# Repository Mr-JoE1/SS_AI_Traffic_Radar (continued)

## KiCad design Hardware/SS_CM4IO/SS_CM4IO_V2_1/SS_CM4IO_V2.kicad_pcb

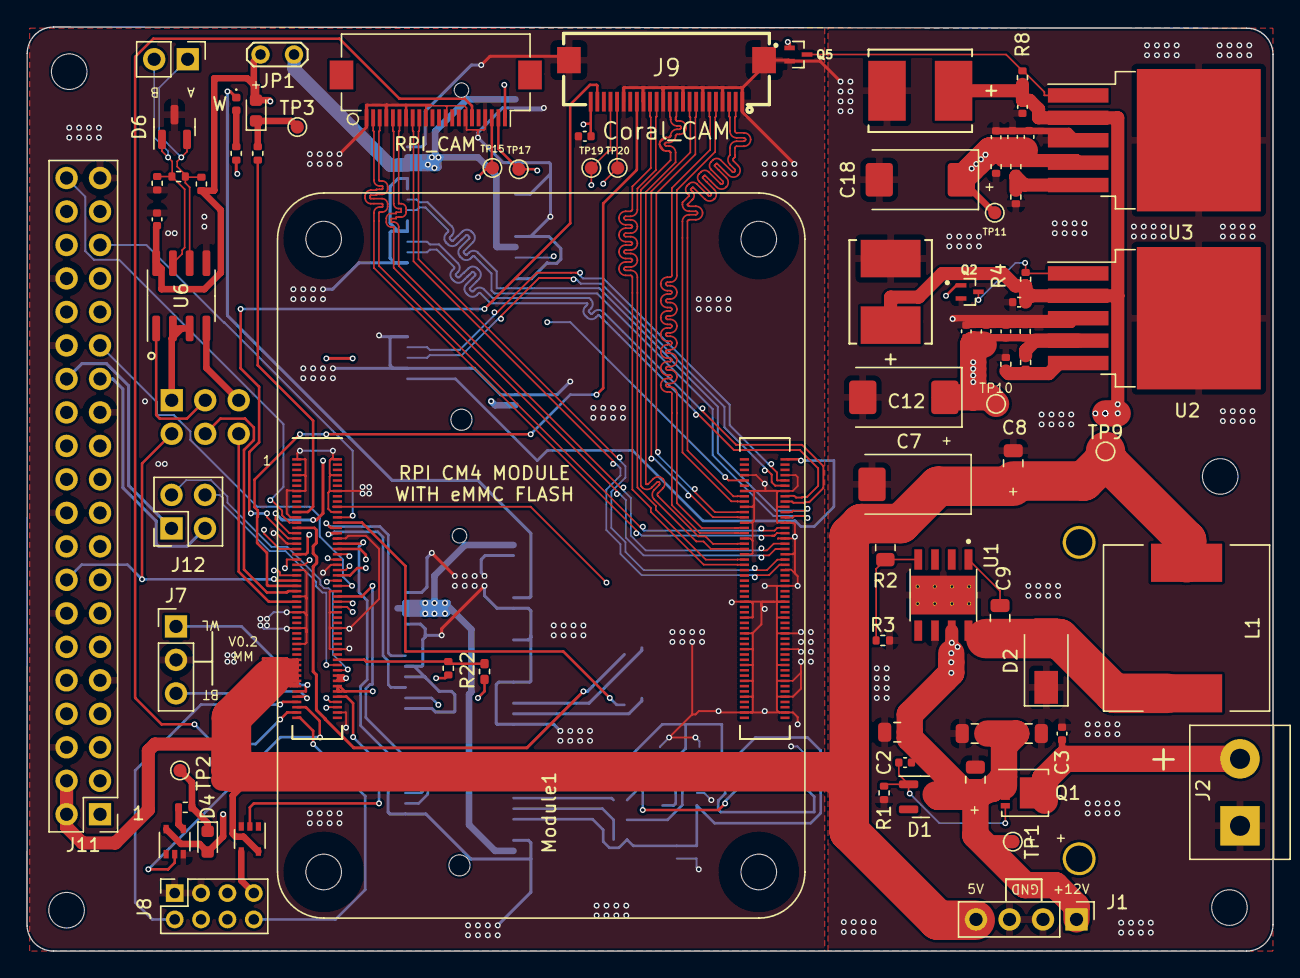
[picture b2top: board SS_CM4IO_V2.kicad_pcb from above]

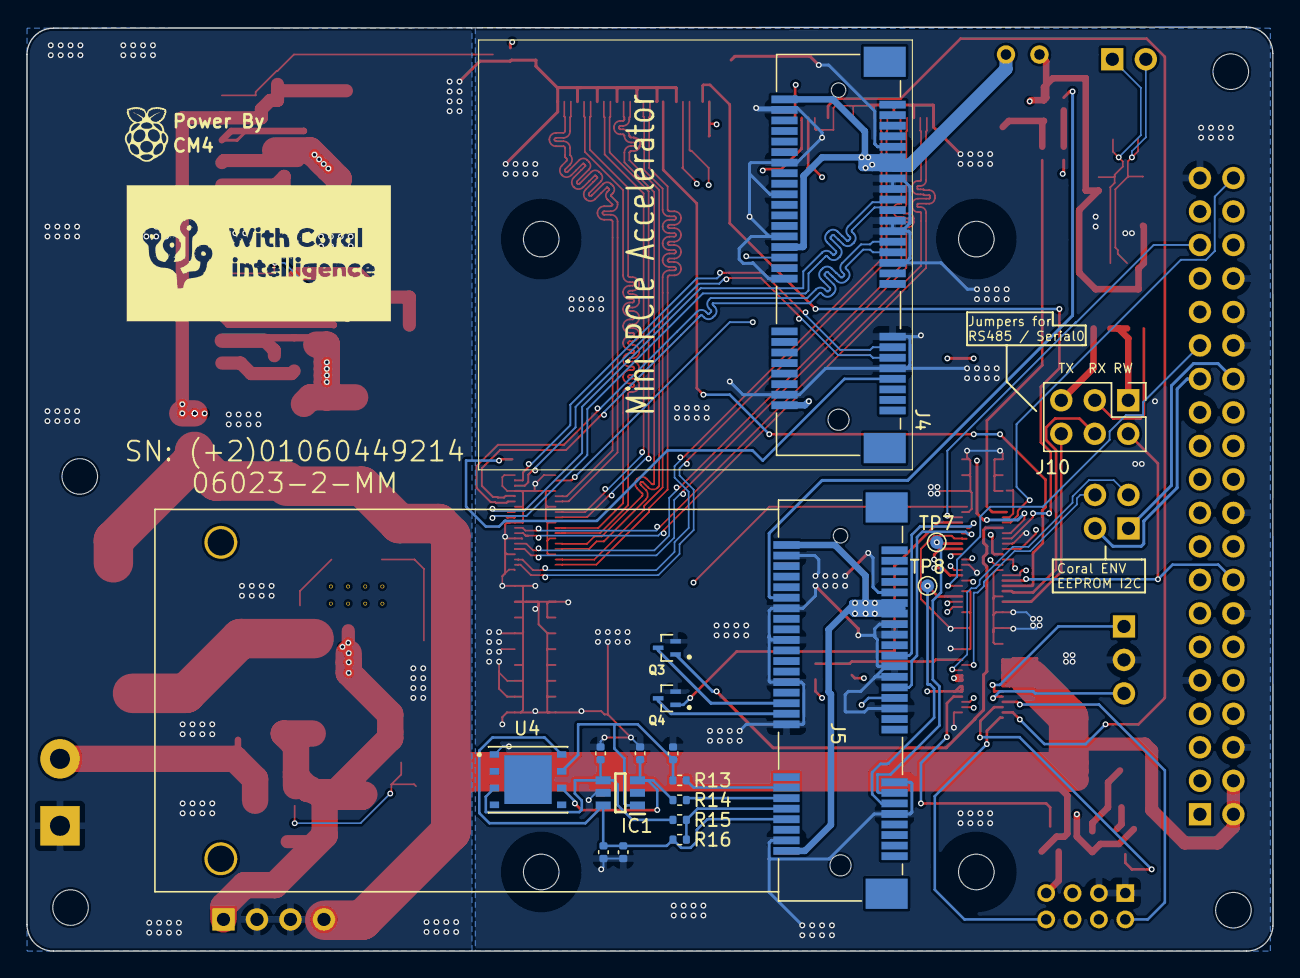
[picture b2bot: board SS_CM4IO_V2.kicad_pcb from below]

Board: 4 copper layers, 94.5 x 70.1 mm, 103 parts (18 on the bottom side), 47 nets.

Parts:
C1: 10u 35v; C_0805_2012Metric
C2, C3: 100n 100v; C_0402_1005Metric
C4, C5: 4.7uF; C_0805_2012Metric
C6, C8, C9: 0.01uF; C_0805_2012Metric
C7: 330uF; CP_EIA-7343-31_Kemet-D
C10, C16: 470uF; Kemet _3760_H
C11, C13, C17, C19, C26: 100n; C_0402_1005Metric
C12, C18: 470uF; CP_EIA-7343-31_Kemet-D
C14, C20, C22, C23, C24, C25: 33p; C_0402_1005Metric
C15, C21: 10p; C_0402_1005Metric
C27: 104; C_0402_1005Metric
C28: 1u; C_0402_1005Metric
CM4_A, CM4_B: DF40C-100DS; DF40C-100DS_CM4
D1: MMBZ5242BLT1G; SOT-23
D2: SS54; D_SMA
D3: W; LED_0402_1005Metric
D4: LED Red; LED_0603_1608Metric
D5: LED Green; LED_0603_1608Metric
D6: PSM712-LF-T7; SOT-23
H1, H2, H3, H4: MountingHole; MountingHole_2.7mm_M2.5
IC1: DALC208SC6; SOT95P280X145-6N
J1: AMP171826-4; PinHeader_1x04_P2.54mm_Vertical
J2: pwr; TerminalBlock_bornier-2_P5.08mm
J3: RPI_CAM; Hirose_FH12-22S-0.5SH_1x22-1MP_P0.50mm_Horizontal
J4, J5: Bus_PCI_Express_Mini; BUS_PCI_Express_Mini_Half
J6: Conn_01x02_Male; PinHeader_1x02_P2.54mm_Vertical
J7: W.BT; PinHeader_1x03_P2.54mm_Vertical
J8: Conn_02x04_Odd_Even; PinSocket_2x04_P2.00mm_Vertical
J9: Coral_CAM; FPC-SMD_P0.50-24P_QCHF-SM-H2.0
J10: RADAR_EN; PinHeader_2x03_P2.54mm_Vertical
J11: ENV_SEN; PinHeader_2x20_P2.54mm_Vertical
J12: EPP_RW; PinSocket_2x02_P2.54mm_Vertical
JP1: Jumper_2_Open; TestPoint_2Pads_Pitch2.54mm_Drill0.8mm
L1: CDRH127/LDNP-150MC; L_12x12mm_H8mm
Module1: ComputeModule4; Raspberry-Pi-4-Compute-Module
Q1: DMP3013SFV-7; Diodes_PowerDI3333-8
Q2, Q3, Q4, Q5: DTC143ZEBTL; SOTFL50P160X85-3N
R1: 12K 1%; R_0402_1005Metric
R2: 10K; R_0805_2012Metric
R3: 3.16K; R_0402_1005Metric
R4, R8: 51K; R_0402_1005Metric
R5, R9: 82K 1%; R_0402_1005Metric
R6, R10: 470R; R_0402_1005Metric
R7, R11: 47K 1%; R_0402_1005Metric
R12: 1K; R_0402_1005Metric
R13, R14, R15: 22R; R_0402_1005Metric
R16: 15R; R_0402_1005Metric
R17, R18: 1k; R_0402_1005Metric
R19, R20: 360R; R_0402_1005Metric
R21: 0R; R_0402_1005Metric
R22: nf; R_0402_1005Metric_Pad0.72x0.64mm_HandSolder
R23: 120R; R_0402_1005Metric
TP1: 12V; TestPoint_Pad_D1.0mm
TP2, TP3, TP7, TP8, TP9, TP10, TP11, TP15, TP17, TP19, TP20: TestPoint; TestPoint_Pad_D1.0mm
U1: TPS5450DDAR; CONV_TPS5450DDAR
U2, U3: MIC29302WU; TO-263-5_TabPin3
U4: SIM-E-MFF2-GL-250; PSON127P500X600X82-9N
U5, U7: 74LVC1G07SE-7; SOT-353_SC-70-5
U6: MAX3485; SOIC-8_3.9x4.9mm_P1.27mm

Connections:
/4G_GSM/+3v3_GSM: C18.1, C19.1, C20.1, C21.1, J5.2 (+3V3AUX), J5.39 (+3V3AUX), J5.41 (+3V3AUX), J5.52 (+3V3AUX), R9.1, R10.1, R12.2, TP11.1, U3.4 (VOUT)
/4G_GSM/GSM_UART_RX: J5.11 (REFCLK-), TP8.1
/4G_GSM/GSM_UART_TX: J5.13 (REFCLK+), TP7.1
/4G_GSM/LED_WWAN: D3.1 (K), J5.42 (~LED_WWAN)
/4G_GSM/PERST: J5.22 (~PERST), Q3.3 (C)
/4G_GSM/USIM_CLK: J5.12 (UIM_CLK), R14.1
/4G_GSM/USIM_DATA: J5.10 (UIM_DATA), R15.1, R16.2
/4G_GSM/USIM_RST: J5.14 (~UIM_RESET), R13.1
/4G_GSM/USIM_VDD: C22.2, C26.1, IC1.6 (I/O_4), J5.8 (UIM_PWR), R16.1, U4.8 (VCC)
/4G_GSM/W_DISABLE: J5.20 (~W_DISABLE), Q4.3 (C)
/+3v3_PCIe: C12.1, C13.1, C14.1, C15.1, J4.2 (+3V3AUX), J4.24 (+3V3AUX), J4.39 (+3V3AUX), J4.41 (+3V3AUX), J4.52 (+3V3AUX), JP1.1 (A), R5.1, R6.1, TP10.1, U2.4 (VOUT)
/+5R: C7.1, C8.1, J1.4, J11.2, J11.4, L1.2, R2.1, TP9.1, U7.5 (VCC)
/+12v: C1.1, C2.1, C4.1, C5.1, C6.1, C10.1, C11.1, C16.1, C17.1, D1.3 (K), J1.1, Q1.1 (S), Q1.2 (S), Q1.3 (S), R4.1, R8.1, TP1.1, U1.7 (VIN), U2.2 (VIN), U3.2 (VIN)
/CM4_MOD/CM4_3.3v: C27.1, C28.1, D4.2 (A), D5.2 (A), J3.22, J9.24, J11.1, JP1.2 (B), R20.2, R21.1, U5.5 (VCC), U6.8 (VCC)
/CM4_MOD/CONSOL_RX: J10.4, J11.10
/CM4_MOD/CONSOL_TX: J10.6, J11.8
/CM4_MOD/EEP_SCL: J11.28, J12.1
/CM4_MOD/EEP_SDA: J11.27, J12.2
/CM4_MOD/ENV_BTN: J10.2, J11.16
/CM4_MOD/GPIO_VREF: R21.2, R22.2
/CM4_MOD/RS485_RW: J10.1, U6.2 (~RE), U6.3 (DE)
/CM4_MOD/RS485_RX: J10.3, U6.1 (RO)
/CM4_MOD/RS485_TX: J10.5, U6.4 (DI)
/CM4_MOD/RS+: D6.2 (K2), J6.1, R20.1, R23.2, U6.6 (A)
/CM4_MOD/RS-: D6.1 (K1), J6.2, R19.2, R23.1, U6.7 (B)
/CM4_MOD/SCA0: J9.21, J12.3, TP19.1
/CM4_MOD/SCL0: J9.20, J12.4, TP20.1
/PCIe_CAM/ID_SC: J3.20, TP15.1
/PCIe_CAM/ID_SD: J3.21, TP17.1
/PSUs/VSNS1: R2.2, R3.1, U1.4 (VSENSE)
GND: C1.2, C3.2, C4.2, C5.2, C6.2, C7.2, C8.2, C10.2, C11.2, C12.2, C13.2, C14.2, C15.2, C16.2, C17.2, C18.2, C19.2, C20.2, C21.2, C22.1, C23.1, C24.1, C25.1, C26.2, C27.2, C28.2, D2.1 (A), D6.3 (A), IC1.5 (REF_1), J1.2, J1.3, J2.1, J3.1, J3.4, J3.7, J3.10, J3.13, J3.16, J3.19, J4.4 (GND), J4.9 (GND), J4.15 (GND), J4.18 (GND), J4.21 (GND), J4.26 (GND), J4.27 (GND), J4.29 (GND), J4.34 (GND), J4.35 (GND), J4.37 (GND), J4.40 (GND), J4.43 (GND), J4.50 (GND), J5.4 (GND), J5.9 (GND), J5.15 (GND), J5.18 (GND), J5.21 (GND), J5.26 (GND), J5.27 (GND), J5.29 (GND), J5.34 (GND), J5.35 (GND), J5.37 (GND), J5.40 (GND), J5.43 (GND), J5.50 (GND), J7.2, J8.1, J8.3, J9.1, J9.4, J9.7, J9.10, J9.13, J9.16, J9.19, J9.25, J9.26, J11.6, J11.9, J11.14, J11.20, J11.25, J11.30, J11.34, J11.39, Q2.2 (E), Q3.2 (E), Q4.2 (E), Q5.2 (E), R1.2, R3.2, R6.2, R7.2, R10.2, R11.2, R19.1, U1.6 (GND), U1.9 (POWERPAD), U2.3 (GND), U3.3 (GND), U4.1 (GND), U5.3 (GND), U6.5 (GND), U7.3 (GND)
unnamed: C2.2, D1.1 (A), Q1.4 (G), R1.1
unnamed: C3.1, J2.2, Q1.5 (D)
unnamed: C9.1, U1.1 (BOOT)
unnamed: C9.2, D2.2 (K), L1.1, U1.8 (PH)
unnamed: C23.2, IC1.1 (I/O_1), R13.2, U4.7 (RST)
unnamed: C24.2, IC1.3 (I/O_2), R14.2, U4.6 (CLK)
unnamed: C25.2, IC1.4 (I/O_3), R15.2, U4.3 (I/O)
unnamed: D3.2 (A), R12.1
unnamed: D4.1 (K), R17.1, TP2.1
unnamed: D5.1 (K), R18.1, TP3.1
unnamed: J8.7, U7.4
unnamed: Q2.3 (C), R4.2, U2.1 (EN)
unnamed: Q5.3 (C), R8.2, U3.1 (EN)
unnamed: R5.2, R7.1, U2.5 (ADJ)
unnamed: R9.2, R11.1, U3.5 (ADJ)
unnamed: R17.2, U5.4

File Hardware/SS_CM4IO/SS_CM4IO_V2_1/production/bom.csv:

Designator,Footprint,Quantity,Value,LCSC Part #
C1,805,1,10u 35v,C15850
"C10, C16",Kemet _3760_H,2,470uF,C600599
"C11, C13, C17, C19, C26",402,5,100n,C307331
"C12, C18",CP_EIA-7343-31_Kemet-D,2,470uF,C116576
"C14, C20, C22, C23, C24, C25",402,6,33p,C107005
"C15, C21",402,2,10p,C513681
"C2, C3",402,2,100n 100v,C307331
C27,402,1,104,C307331
C28,402,1,1u,C107005
"C4, C5",805,2,4.7uF,C318563
"C6, C8, C9",805,3,0.01uF,C60133
C7,CP_EIA-7343-31_Kemet-D,1,330uF,C105408
"CM4_A, CM4_B",DF40C-100DS_CM4,2,DF40C-100DS,C597931
D1,SOT-23,1,MMBZ5242BLT1G,C236184
D2,D_SMA,1,SS54,C908681
D3,402,1,W,C130724
D4,603,1,LED Red,C84263
D5,603,1,LED Green,C434423
D6,SOT-23,1,PSM712-LF-T7,C32677
IC1,SOT95P280X145-6N,1,DALC208SC6,C5123934
J1,PinHeader_1x04_P2.54mm_Vertical,1,AMP171826-4,C5116483
J10,PinHeader_2x03_P2.54mm_Vertical,1,RADAR_EN,C5116482
J11,PinHeader_2x20_P2.54mm_Vertical,1,ENV_SEN,
J12,PinSocket_2x02_P2.54mm_Vertical,1,EPP_RW,
J2,TerminalBlock_bornier-2_P5.08mm,1,pwr,C3018698
J3,Hirose_FH12-22S-0.5SH_1x22-1MP_P0.50mm_Horizontal,1,RPI_CAM,C597981
"J4, J5",BUS_PCI_Express_Mini_Half,2,Bus_PCI_Express_Mini,C266899
J6,PinHeader_1x02_P2.54mm_Vertical,1,Conn_01x02_Male,C2905414
J7,PinHeader_1x03_P2.54mm_Vertical,1,W.BT,C5116482
J8,PinSocket_2x04_P2.00mm_Vertical,1,Conn_02x04_Odd_Even,C5156676
J9,FPC-SMD_P0.50-24P_QCHF-SM-H2.0,1,Coral_CAM,C262683
L1,L_12x12mm_H8mm,1,CDRH127/LDNP-150MC,C879410
Q1,Diodes_PowerDI3333-8,1,DMP3013SFV-7,C264098
"Q2, Q3, Q4, Q5",SOTFL50P160X85-3N,4,DTC143ZEBTL,C308696
R1,402,1,12K 1%,C144798
"R10, R6",402,2,470R,C25117
"R11, R7",402,2,47K 1%,C93943
"R12, R17, R18",402,3,1K,C106235
"R13, R14, R15",402,3,22R,C25092
R16,402,1,15R,C138052
R19,402,1,360R,C2930003
R2,805,1,10K,C17414
R20,402,1,360R ,C2930003
R21,402,1,0R,C21376
R23,402,1,120R,C114758
R3,402,1,3.16K,C2692899
"R4, R8",402,2,51K,C25794
"R5, R9",402,2,82K 1%,C137932
U1,CONV_TPS5450DDAR,1,TPS5450DDAR,C114425 
"U2, U3",TO-263-5_TabPin3,2,MIC29302WU,C11149
"U5, U7",SOT-353_SC-70-5,2,74LVC1G07SE-7,C12511
U6,SOIC-8_3.9x4.9mm_P1.27mm,1,MAX3485,C9943

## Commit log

2023-10-18 Maher Work
2023-11-12 phone seatbelt dataset
